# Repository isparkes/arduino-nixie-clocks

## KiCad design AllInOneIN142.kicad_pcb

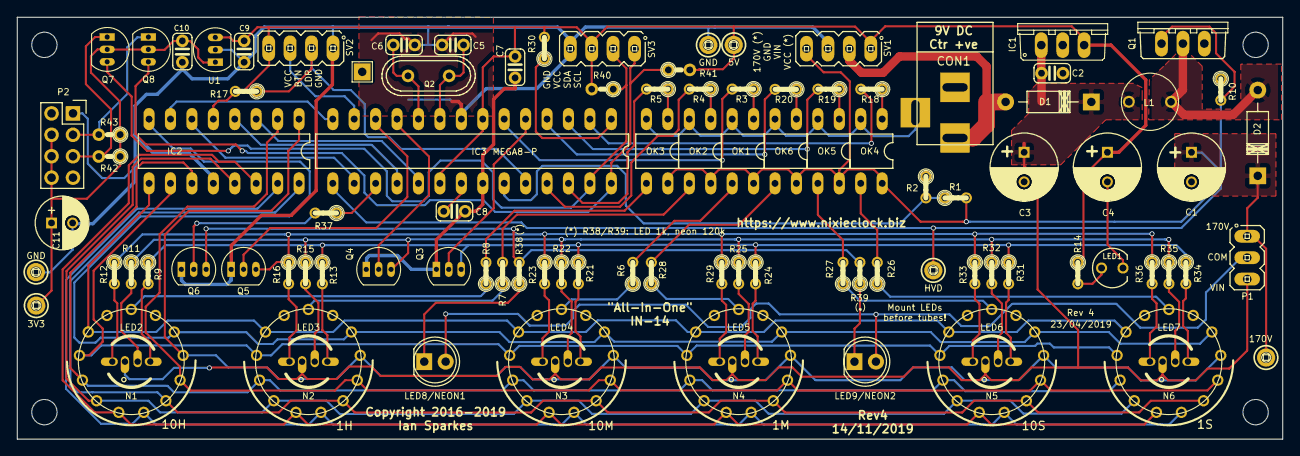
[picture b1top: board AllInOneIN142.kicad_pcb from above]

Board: 2 copper layers, 150.0 x 50.0 mm, 107 parts (0 on the bottom side), 88 nets.

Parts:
C1: 2.2uF; C_Radial_D8_L11.5_P3.5
C2, C7, C8, C9, C10: 100nF; C025-024X044
C3, C4: 220uF; C_Radial_D8_L11.5_P3.5
C5, C6: 22pF; C025-024X044
C11: 10uF; C_Radial_D6.3_L11.2_P2.5
CON1: BARREL_JACK
D1: 1N4001; Diode_DO-41_1N4001
D2: UF4004/7; Diode_DO-41_1N4001
GND Can: TestPoint_THTPad_2.0x2.0mm_Drill1.0mm
IC1: 7805; 7805_TO220V
IC2: 74141N; 74141_DIL16
IC3: MEGA8-P; 328P_DIL28
L1: 100uH; Inductor-100mH
LED1: Power; LED_3MM
LED2, LED3, LED4, LED5, LED6: LED_RAGB; LED5_RGB_CA_Offset_Tighter
LED7: LEDs2_RAGB; LED5_RGB_CA_Offset_Tighter
LED8/NEON1, LED9/NEON2: LED; LED-5MM-Centred
MH1, MH2, MH3, MH4: MountingHole_3mm
N1, N2, N3, N4, N5, N6: IN-14
OK1, OK2, OK3, OK4, OK5, OK6: EL817C; optocoupler-DIL04
P1: CONN_01X03; Header_MA03-1
P2: ESP8266-01_02X04; ESP8266_2x04
Q1: IRF840; TRANSISTOR-POWER_TO220BV
Q2: 16MHz; Crystal_HC49-U_Vertical
Q3, Q4, Q5, Q6: 2N7000; TO-92_inline_MPSA42
Q7, Q8: 2N7000; TO-92_2N7000_inline
R1: 390k; R-0207_2V
R2: 4.7k; R-0207_2V
R3, R4, R5, R9, R11, R12, R13, R15, R16, R18, R19, R20, R21, R22, R23, R24, R25, R29, R31, R32, R33, R34, R35, R36, R37, R38, R39: 1k; R-0207_2V
R6, R7, R8, R10, R14, R26, R27, R28: 3k; R-0207_2V
R17, R30, R40, R41, R42, R43: 10k; R-0207_2V
SV1: PWR; Header_MA04-1
SV2: CONN_FRONT; Header_MA04-1
SV3: CONN_RTC; Header_MA04-1
U1: L78L05_TO92; TO-92_2N7000_inline
W1: 5V; TESTPAD_P1-13
W2, W4: GND; TESTPAD_P1-13
W3: 170V; TESTPAD_P1-13
W5: HVD; TESTPAD_P1-13
W6: 3V3; TESTPAD_P1-13

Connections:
/3V3: C10.1, C11.1, P2.4, P2.6, P2.8, Q7.2, Q8.2, R42.1, R43.1, U1.1, W6.1
/170V: C1.1, D2.1, OK1.4, OK2.4, OK3.4, OK4.4, OK5.4, OK6.4, P1.1, R1.2, SV1.4, W3.1
/ANODE1: IC3.26, R5.2
/ANODE2: IC3.25, R4.2
/ANODE3: IC3.6, R3.2
/ANODE4: IC3.4, R20.2
/ANODE5: IC3.3, R19.2
/ANODE6: IC3.2, R18.2
/BTN1: IC3.13, SV2.3
/B_LED_DRIVE: Q3.3, R9.1, R13.1, R21.1, R24.1, R31.1, R34.1
/B_LED_GATE: IC3.5, Q3.2
/CATHODE_0: IC2.8, N1.0, N2.0, N3.0, N4.0, N5.0, N6.0
/CATHODE_1: IC2.9, N1.1, N2.1, N3.1, N4.1, N5.1, N6.1
/CATHODE_2: IC2.10, N1.2, N2.2, N3.2, N4.2, N5.2, N6.2
/CATHODE_3: IC2.11, N1.3, N2.3, N3.3, N4.3, N5.3, N6.3
/CATHODE_4: IC2.13, N1.4, N2.4, N3.4, N4.4, N5.4, N6.4
/CATHODE_5: IC2.14, N1.5, N2.5, N3.5, N4.5, N5.5, N6.5
/CATHODE_6: IC2.15, N1.6, N2.6, N3.6, N4.6, N5.6, N6.6
/CATHODE_7: IC2.16, N1.7, N2.7, N3.7, N4.7, N5.7, N6.7
/CATHODE_8: IC2.2, N1.8, N2.8, N3.8, N4.8, N5.8, N6.8
/CATHODE_9: IC2.1, N1.9, N2.9, N3.9, N4.9, N5.9, N6.9
/CON_AN_1: N1.A, R8.1
/CON_AN_2: N2.A, R7.1
/CON_AN_3: N3.A, R6.1
/CON_AN_4: N4.A, R28.1
/CON_AN_5: N5.A, R27.1
/CON_AN_6: N6.A, R26.1
/DIGIT_A: IC2.3, IC3.19
/DIGIT_B: IC2.6, IC3.16
/DIGIT_C: IC2.7, IC3.14
/DIGIT_D: IC2.4, IC3.18
/DLS: IC3.24, R17.1, SV2.2
/G_LED_DRIVE: Q4.3, R11.1, R15.1, R22.1, R25.1, R32.1, R35.1
/G_LED_GATE: IC3.11, Q4.2
/HVD: IC3.15, Q1.G, R10.2, W5.1
/HVS: IC3.23, R1.1, R2.2
/I_A1: OK3.1, R5.1
/I_A2: OK2.1, R4.1
/I_A3: OK1.1, R3.1
/I_A4: OK6.1, R20.1
/I_A5: OK5.1, R19.1
/I_A6: OK4.1, R18.1
/MOSI: IC3.17, R37.1
/O_A1: OK3.3, R8.2
/O_A2: OK2.3, R7.2
/O_A3: OK1.3, R6.2
/O_A4: OK6.3, R28.2
/O_A5: OK5.3, R27.2
/O_A6: OK4.3, R26.2
/PWR_HV_PULSE: D2.2, L1.1, Q1.D
/PWR_INPUT: CON1.1, D1.2, SV1.2
/PWR_VIN: C2.2, C3.1, D1.1, IC1.1, L1.2, LED2.2, LED3.2, LED4.2, LED5.2, LED6.2, LED7.2, P1.3
/RESET: IC3.1, R30.1
/R_LED_DRIVE: Q5.3, R12.1, R16.1, R23.1, R29.1, R33.1, R36.1
/R_LED_GATE: IC3.12, Q5.2
/SCL: IC3.28, Q8.3, R41.1, SV3.1
/SDA: IC3.27, Q7.3, R40.1, SV3.2
/TICK_LED_1: LED8/NEON1.1, R38.1
/TICK_LED_2: LED9/NEON2.1, R39.1
/TICK_LED_GATE: Q6.2, R37.2
/VCC: C4.1, C7.1, C9.1, IC1.3, IC2.5, IC3.7, IC3.20, R14.1, R17.2, R30.2, R40.2, R41.2, SV1.1, SV2.4, SV3.3, U1.3, W1.1
/XTAL1: C5.2, IC3.9, Q2.2
/XTAL2: C6.1, IC3.10, Q2.1
GND: C1.2, C2.1, C3.2, C4.2, C5.1, C6.2, C7.2, C8.1, C9.2, C10.2, C11.2, CON1.2, CON1.3, IC1.2, IC2.12, IC3.8, IC3.22, LED1.K, OK1.2, OK2.2, OK3.2, OK4.2, OK5.2, OK6.2, P2.1, Q1.S, Q3.1, Q4.1, Q5.1, Q6.1, R2.1, R10.1, SV1.3, SV2.1, SV3.4, U1.2, W2.1, W4.1
unnamed: C8.2, IC3.21
unnamed: LED1.A, R14.2
unnamed: LED2.1, R12.2
unnamed: LED2.3, R11.2
unnamed: LED2.4, R9.2
unnamed: LED3.1, R16.2
unnamed: LED3.3, R15.2
unnamed: LED3.4, R13.2
unnamed: LED4.1, R23.2
unnamed: LED4.3, R22.2
unnamed: LED4.4, R21.2
unnamed: LED5.1, R29.2
unnamed: LED5.3, R25.2
unnamed: LED5.4, R24.2
unnamed: LED6.1, R33.2
unnamed: LED6.3, R32.2
unnamed: LED6.4, R31.2
unnamed: LED7.1, R36.2
unnamed: LED7.3, R35.2
unnamed: LED7.4, R34.2
unnamed: LED8/NEON1.2, LED9/NEON2.2, P1.2
unnamed: P2.3, Q8.1, R43.2
unnamed: P2.5, Q7.1, R42.2
unnamed: Q6.3, R38.2, R39.2

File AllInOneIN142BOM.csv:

"Id";"Designator";"Package";"Quantity";"Designation";"Supplier and ref";
1;"W2,W2";"Measurement_Point_Round-TH_Big";2;"GND";;;
2;"C5,C6";"rcl-C050-024X044";2;"22pF";;;
3;"LED9,LED8";"LED-5MM-Centred";2;"LED";;;
4;"C1";"C_Radial_D8_L11.5_P3.5";1;"2.2uF";;;
5;"C3,C4";"C_Radial_D8_L11.5_P3.5";2;"220uF";;;
6;"W1";"Measurement_Point_Round-TH_Big";1;"VCC";;;
7;"W3";"Measurement_Point_Round-TH_Big";1;"170V";;;
8;"LED2,LED7,LED6,LED5,LED4,LED3";"LED5_RGB_CA";6;"LED_RAGB";;;
9;"Q2";"Crystal_HC49-U_Vertical";1;"16MHz";;;
10;"D2";"Diode_DO-41_1N4001";1;"UF4004/7";;;
11;"D1";"Diode_DO-41_1N4001";1;"1N4001";;;
12;"REF**,REF**,REF**,REF**";"MountingHole_3mm";4;"MountingHole_3mm";;;
13;"IC2";"74141_DIL16";1;"74141N";;;
14;"R2";"R-0207_2V";1;"4.7k";;;
15;"R1";"R-0207_2V";1;"390k";;;
16;"R14,R7,R8,R28,R27,R26,R6,R10";"R-0207_2V";8;"3k";;;
17;"R13,R12,R9,R11,R3,R19,R18,R23,R39,R20,R21,R22,R24,R25,R29,R31,R32,R33,R34,R35,R36,R37,R38,R4,R5,R15,R16";"R-0207_2V";27;"1k";;;
18;"R30,R17";"R-0207_2V";2;"10k";;;
19;"IC3";"328P_DIL28";1;"MEGA8-P";;;
20;"OK1,OK2,OK3,OK4,OK5,OK6";"optocoupler-DIL04";6;"EL817C";;;
21;"SV2";"Header_MA04-1";1;"CONN_FRONT";;;
22;"SV3";"Header_MA04-1";1;"CONN_RTC";;;
23;"SV1";"Header_MA04-1";1;"PWR";;;
24;"Q3,Q4,Q5,Q6";"2N7000_TO92";4;"2N7000";;;
25;"C7,C2,C8";"rcl-C050-024X044";3;"100nF";;;
26;"P1";"Header_MA03-1";1;"CONN_01X03";;;
27;"LED1";"LED_3MM";1;"Power";;;
28;"L1";"Inductor-100mH";1;"100uH";;;
29;"IC1";"7805_TO220V";1;"7805";;;
30;"Q1";"TRANSISTOR-POWER_TO220BV";1;"IRF740";;;
31;"N2,N5,N4,N3,N6,N1";"IN-14";6;"IN-14";;;

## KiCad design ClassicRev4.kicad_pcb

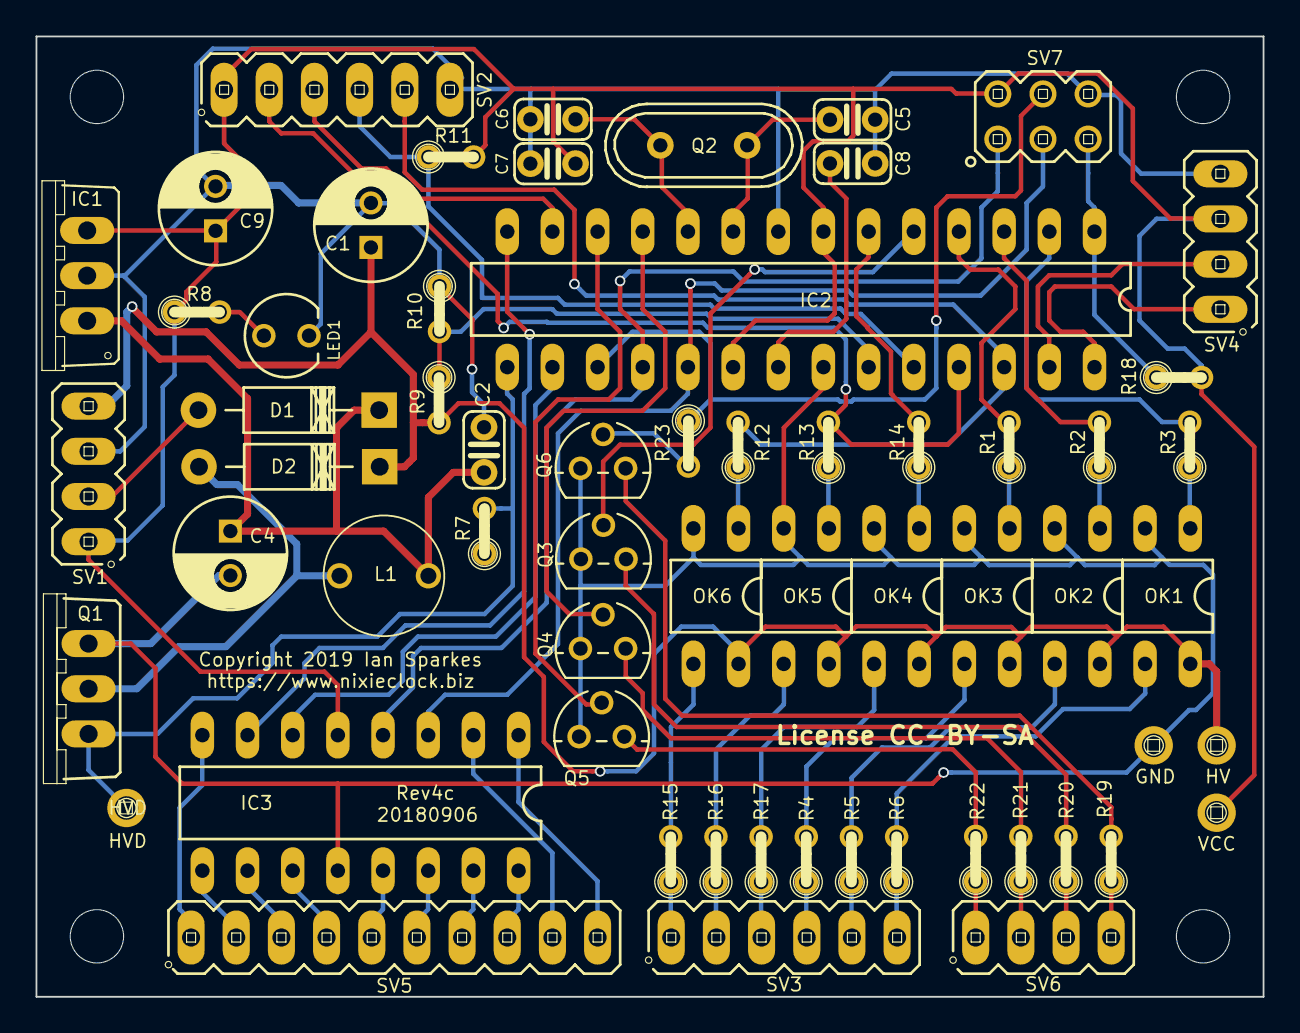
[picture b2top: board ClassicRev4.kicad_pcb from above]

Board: 2 copper layers, 69.0 x 54.0 mm, 65 parts (0 on the bottom side), 68 nets.

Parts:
C1: 2.2uF; C_Radial_D6.3_L11.2_P2.5
C2, C7, C8: 100nF; C025-024X044
C4, C9: 220uF; C_Radial_D6.3_L11.2_P2.5
C5, C6: 22pF; C025-024X044
D1: 1N4001; Diode_DO-41_1N4001
D2: UF4007; Diode_DO-41_1N4001
IC1: 7805TV; 7805_TO220V
IC2: MEGA8-P; 328P_DIL28
IC3: K155ID1; 74141_DIL16
L1: 100uH; Inductor-100mH
LED1: Power; LED_3MM
MH1, MH2, MH3, MH4: MountingHole_3mm
OK1, OK2, OK3, OK4, OK5, OK6: EL817C; optocoupler-DIL04
Q1: IRF740; TRANSISTOR-POWER_TO220BV
Q2: 16MHz; Crystal_HC49-U_Vertical
Q3, Q4, Q5, Q6: 2N7000; 2N7000_TO92
R1, R2, R3, R12, R13, R14, R19, R20, R21, R22, R23: 1k; R-0207_2V
R4, R5, R6, R7, R8, R15, R16, R17: 2.7k; R-0207_2V
R9: 390k; R-0207_2V
R10: 4.7k; R-0207_2V
R11, R18: 10k; R-0207_2V
SV1: PWR; Header_MA04-1
SV2: CONN_FRONT; Header_MA06-1
SV3: CONN_01X06; Header_MA06-1
SV4: CONN_RTC; Header_MA04-1
SV5: CONN_01X10; Header_MA10-1
SV6: CONN_LED; Header_MA04-1
SV7: CONN_ISCP; Header_MA03-2
TP1: HV; TESTPAD_P1-13
TP2: GND; TESTPAD_P1-13
TP3: VCC; TESTPAD_P1-13
TP4: HVD; TESTPAD_P1-13

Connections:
/170V: C1.1, D2.1, OK1.4, OK2.4, OK3.4, OK4.4, OK5.4, OK6.4, R9.2, SV1.4, TP1.1
/ANODE1: IC2.2, R3.2
/ANODE2: IC2.3, R2.2
/ANODE3: IC2.4, R1.2
/ANODE4: IC2.6, R14.2
/ANODE5: IC2.25, R13.2, SV2.2
/ANODE6: IC2.26, R12.2, SV2.5
/AREF: C8.2, IC2.21
/BTN1: IC2.13, SV2.3
/B_GATE: IC2.5, Q3.2
/B_LED: R20.1, SV6.3
/CATHODE_0: IC3.8, SV5.1
/CATHODE_1: IC3.9, SV5.2
/CATHODE_2: IC3.10, SV5.3
/CATHODE_3: IC3.11, SV5.4
/CATHODE_4: IC3.13, SV5.5
/CATHODE_5: IC3.14, SV5.6
/CATHODE_6: IC3.15, SV5.7
/CATHODE_7: IC3.16, SV5.8
/CATHODE_8: IC3.2, SV5.9
/CATHODE_9: IC3.1, SV5.10
/DIGIT_A: IC2.19, IC3.3, SV7.3
/DIGIT_B: IC2.16, IC3.6
/DIGIT_C: IC2.14, IC3.7
/DIGIT_D: IC2.18, IC3.4, SV7.1
/DLS: IC2.24, R11.1, SV2.4
/DRAIN: D2.2, L1.1, Q1.D
/G_GATE: IC2.11, Q4.2
/G_LED: R21.1, SV6.2
/HVD: IC2.15, Q1.G, R7.2, TP4.1
/HVS: IC2.23, R9.1, R10.2
/MOSI: IC2.17, R23.1, SV7.4
/RESET: IC2.1, R18.1, SV7.5
/R_GATE: IC2.12, Q5.2
/R_LED: R22.1, SV6.1
/SCL: IC2.28, SV4.1
/SDA: IC2.27, SV4.2
/TICK_BASE: Q6.2, R23.2
/TICK_LED: R19.1, SV6.4
/VCC: C7.1, C9.1, IC1.3, IC2.7, IC2.20, IC3.5, R8.1, R11.2, R18.2, SV1.1, SV2.1, SV4.3, SV7.2, TP3.1
/VIN: C2.2, C4.1, D1.1, IC1.1, L1.2
/XTAL1: C5.2, IC2.9, Q2.2
/XTAL2: C6.1, IC2.10, Q2.1
GND: C1.2, C2.1, C4.2, C5.1, C6.2, C7.2, C8.1, C9.2, IC1.2, IC2.8, IC2.22, IC3.12, LED1.K, OK1.2, OK2.2, OK3.2, OK4.2, OK5.2, OK6.2, Q1.S, Q3.3, Q4.3, Q5.3, Q6.3, R7.1, R10.1, SV1.3, SV2.6, SV4.4, SV7.6, TP2.1
unnamed: D1.2, SV1.2
unnamed: LED1.A, R8.2
unnamed: OK1.1, R3.1
unnamed: OK1.3, R6.2
unnamed: OK2.1, R2.1
unnamed: OK2.3, R5.2
unnamed: OK3.1, R1.1
unnamed: OK3.3, R4.2
unnamed: OK4.1, R14.1
unnamed: OK4.3, R17.2
unnamed: OK5.1, R13.1
unnamed: OK5.3, R16.2
unnamed: OK6.1, R12.1
unnamed: OK6.3, R15.2
unnamed: Q3.1, R20.2
unnamed: Q4.1, R21.2
unnamed: Q5.1, R22.2
unnamed: Q6.1, R19.2
unnamed: R4.1, SV3.4
unnamed: R5.1, SV3.5
unnamed: R6.1, SV3.6
unnamed: R15.1, SV3.1
unnamed: R16.1, SV3.2
unnamed: R17.1, SV3.3

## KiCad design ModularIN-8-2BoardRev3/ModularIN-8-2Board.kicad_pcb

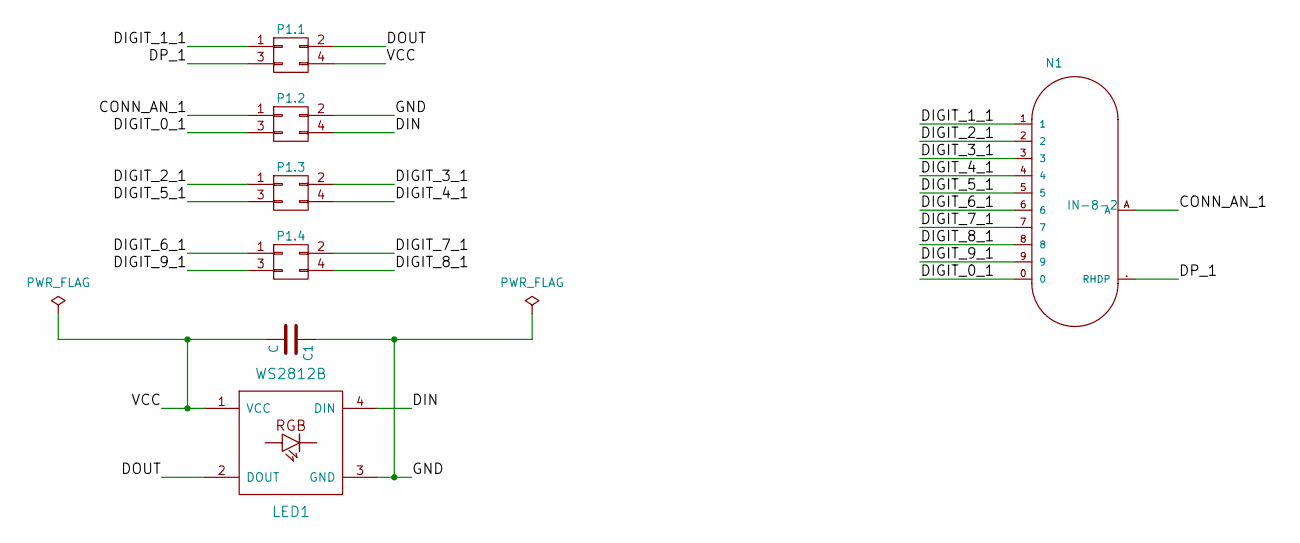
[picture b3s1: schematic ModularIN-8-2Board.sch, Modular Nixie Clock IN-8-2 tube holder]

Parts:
C1: C; C_1206_HandSoldering
LED1: WS2812B
N1: IN-8-2
P1.1, P1.2, P1.3, P1.4: CONN_02X02; Header_MA02-2

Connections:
/CONN_AN_1: N1.A, P1.2.1
/DIGIT_0_1: N1.0, P1.2.3
/DIGIT_1_1: N1.1, P1.1.1
/DIGIT_2_1: N1.2, P1.3.1
/DIGIT_3_1: N1.3, P1.3.2
/DIGIT_4_1: N1.4, P1.3.4
/DIGIT_5_1: N1.5, P1.3.3
/DIGIT_6_1: N1.6, P1.4.1
/DIGIT_7_1: N1.7, P1.4.2
/DIGIT_8_1: N1.8, P1.4.4
/DIGIT_9_1: N1.9, P1.4.3
/DIN: LED1.4 (DIN), P1.2.4
/DOUT: LED1.2 (DOUT), P1.1.2
/DP_1: N1.. (RHDP), P1.1.3
/GND: C1.1, LED1.3 (GND), P1.2.2
/VCC: C1.2, LED1.1 (VCC), P1.1.4

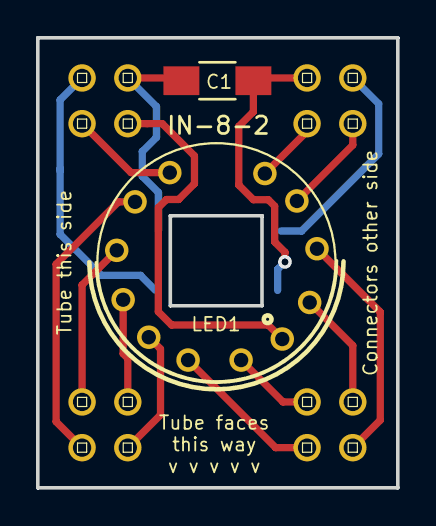
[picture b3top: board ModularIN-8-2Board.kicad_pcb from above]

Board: 2 copper layers, 20.0 x 25.0 mm, 7 parts (0 on the bottom side), 16 nets.

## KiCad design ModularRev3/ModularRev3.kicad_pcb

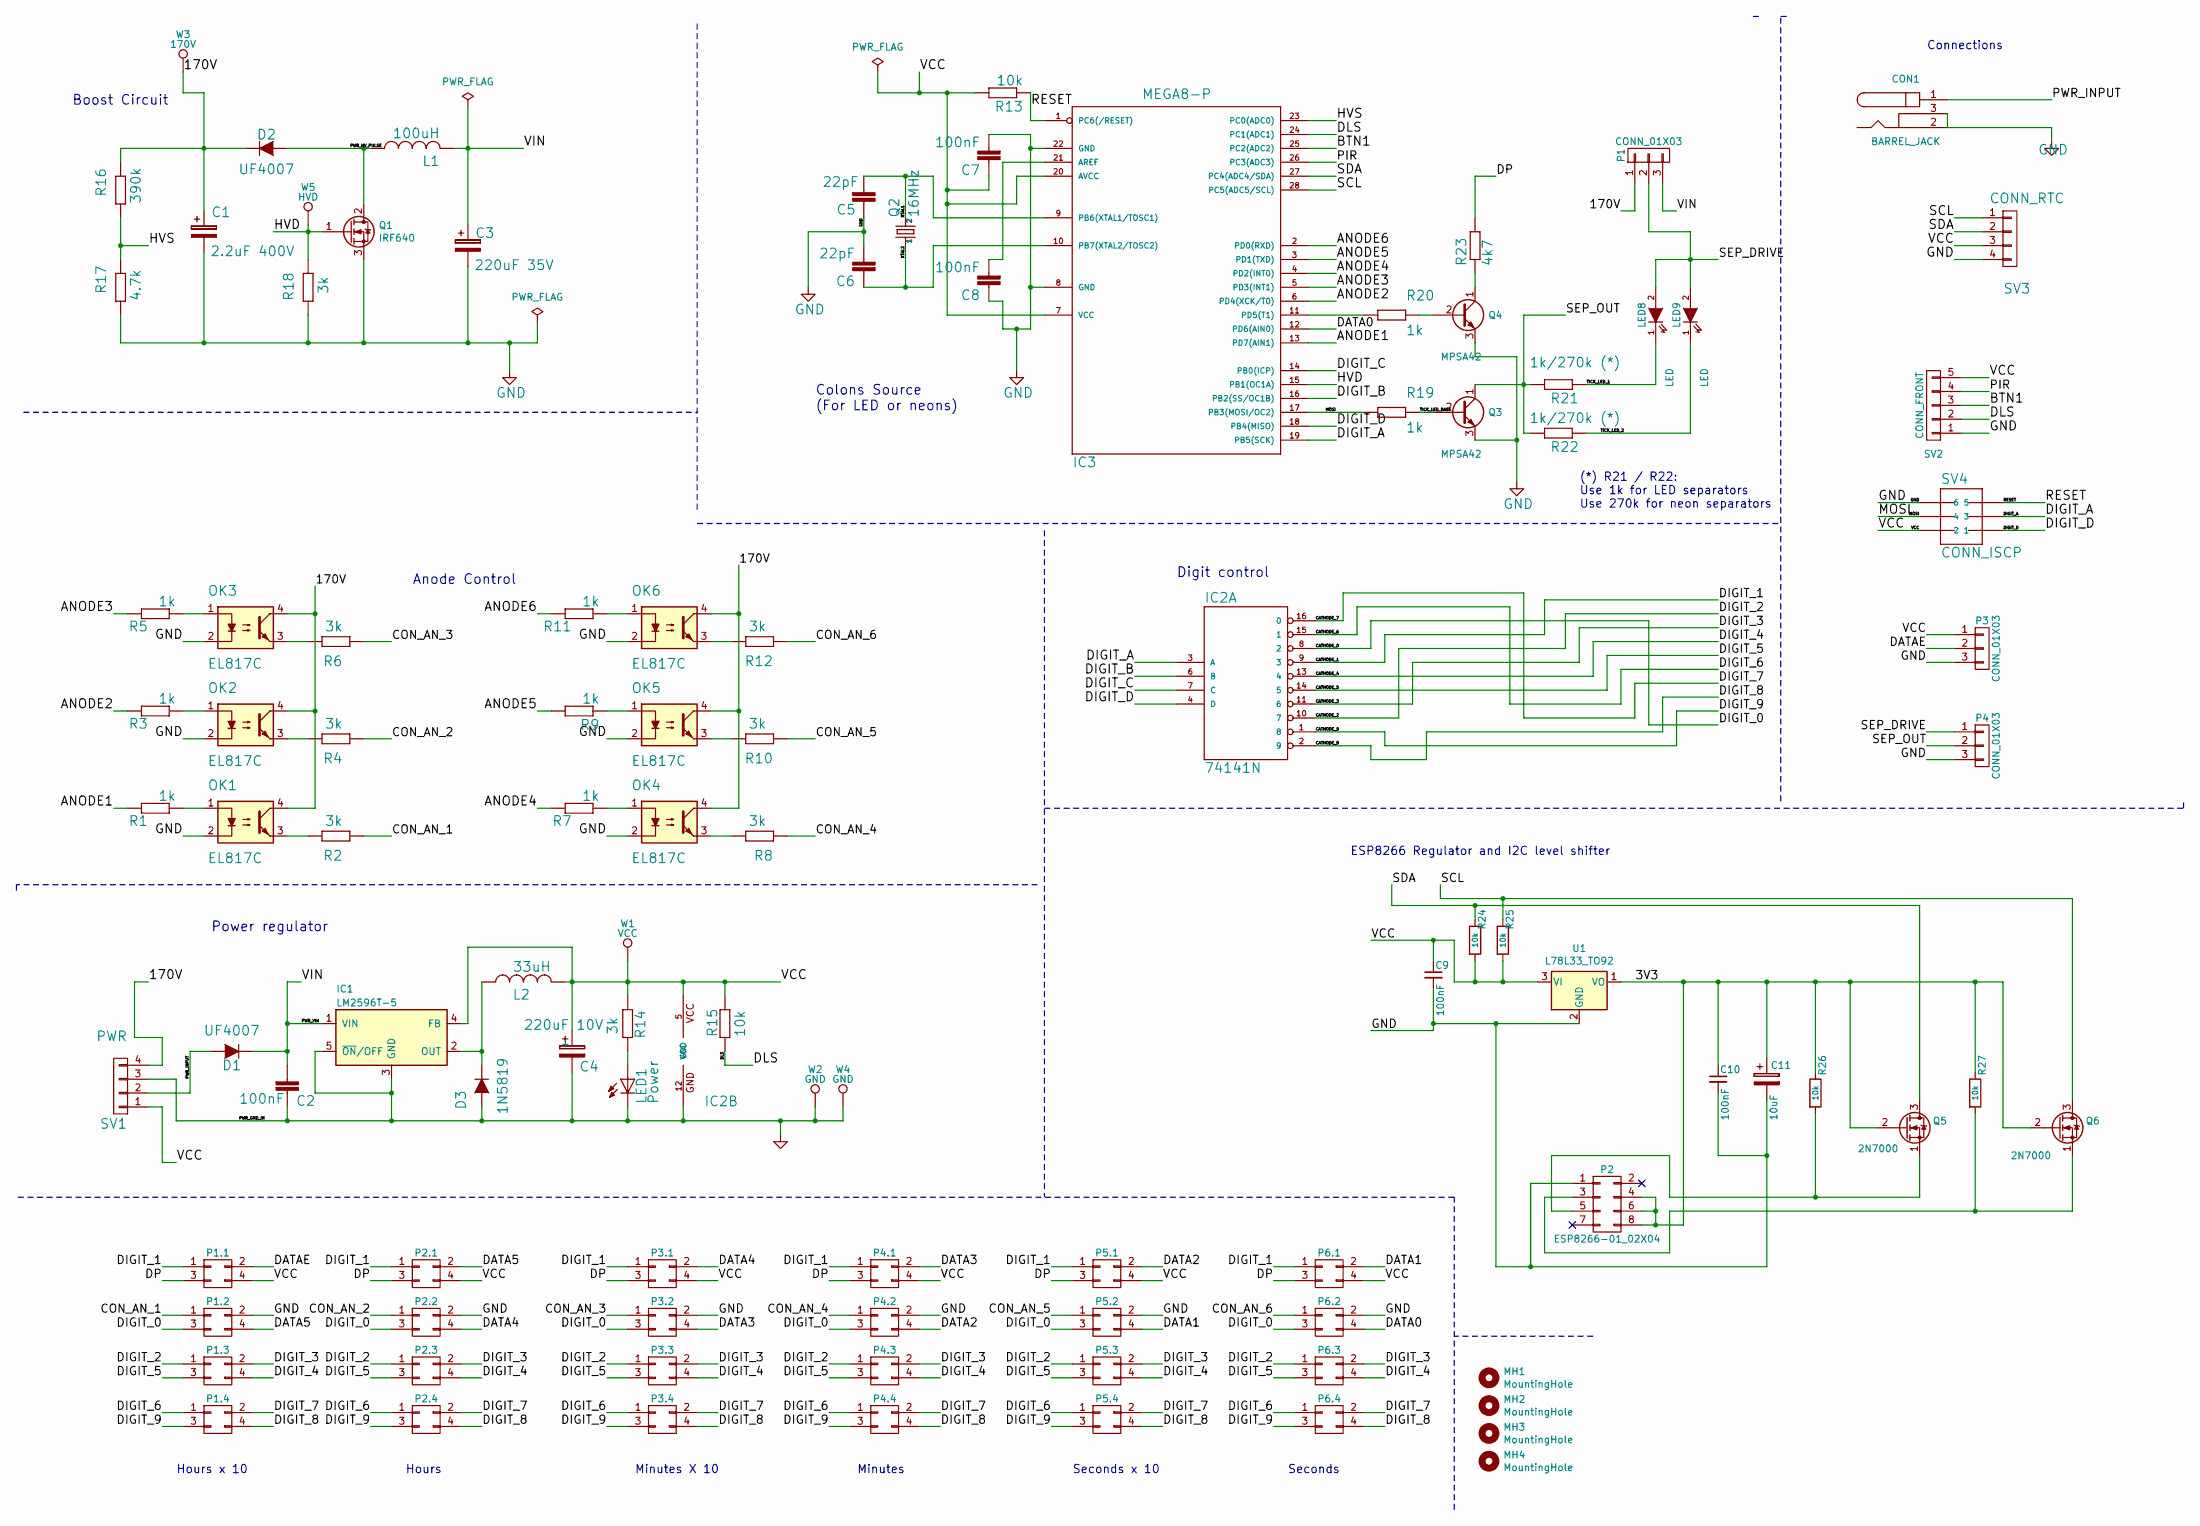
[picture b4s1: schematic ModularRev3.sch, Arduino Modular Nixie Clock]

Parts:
C1: 2.2uF 400V; C_Radial_D10_L11.2_P2.5_3.5_5
C2, C7, C8, C9, C10: 100nF; C025-024X044
C3: 220uF 35V; C_Radial_D6.3_L11.2_P2.5
C4: 220uF 10V; C_Radial_D6.3_L11.2_P2.5
C5, C6: 22pF; C025-024X044
C11: 10uF; C_Radial_D6.3_L11.2_P2.5
CON1: BARREL_JACK
D1, D2: UF4007; Diode_DO-41_1N4001
D3: 1N5819; Diode_DO-41_1N4001
IC1: LM2596T-5; TO220-5A
IC2: 74141N; 74141_DIL16
IC3: MEGA8-P; 328P_DIL28
L1: 100uH; Inductor-100mH
L2: 33uH; Inductor-33mH-TH-SMD
LED1: Power; LED_3MM
LED8, LED9: LED; LED-5MM-Centred
MH1, MH2, MH3, MH4: MountingHole; MountingHole_3.2mm_M3
OK1, OK2, OK3, OK4, OK5, OK6: EL817C; optocoupler-DIL04
P1, P3, P4: CONN_01X03; Header_MA03-1
P1.1, P1.2, P1.3, P1.4, P2.1, P2.2, P2.3, P2.4, P3.1, P3.2, P3.3, P3.4, P4.1, P4.2, P4.3, P4.4, P5.1, P5.2, P5.3, P5.4, P6.1, P6.2, P6.3, P6.4: CONN_02X02; Header_MA02-2
P2: ESP8266-01_02X04; ESP8266_2x04
Q1: IRF640; TO-220-3_H
Q2: 16MHz; Crystal_HC49-U_Vertical
Q3, Q4: MPSA42; 2N7000_TO92
Q5, Q6: 2N7000; TO-92_2N7000_inline
R1, R3, R5, R7, R9, R11, R19, R20: 1k; R-0207_2V
R2, R4, R6, R8, R10, R12, R14, R18: 3k; R-0207_2V
R13, R15, R24, R25, R26, R27: 10k; R-0207_2V
R16: 390k; R-0207_2V
R17: 4.7k; R-0207_2V
R21, R22: 1k/270k (*); R-0207_2V
R23: 4k7; R-0207_2V
SV1: PWR; Header_MA04-1
SV2: CONN_FRONT; Header_MA05-1
SV3: CONN_RTC; Header_MA04-1
SV4: CONN_ISCP; Header_MA03-2
U1: L78L33_TO92; TO-92_Inline
W1: VCC; TESTPAD_P1-13
W2, W4: GND; TESTPAD_P1-13
W3: 170V; TESTPAD_P1-13
W5: HVD; TESTPAD_P1-13

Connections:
/3V3: C10.1, C11.1, P2.4 (CH_EN), P2.6 (RST), P2.8 (VCC), Q5.2 (G), Q6.2 (G), R26.1, R27.1, U1.1 (VO)
/170V: C1.1, D2.1 (K), OK1.4, OK2.4, OK3.4, OK4.4, OK5.4, OK6.4, P1.1, R16.2, SV1.4, W3.1
/ANODE1: IC3.13 (PD7(AIN1)), R1.2
/ANODE2: IC3.6 (PD4(XCK/T0)), R3.2
/ANODE3: IC3.5 (PD3(INT1)), R5.2
/ANODE4: IC3.4 (PD2(INT0)), R7.2
/ANODE5: IC3.3 (PD1(TXD)), R9.2
/ANODE6: IC3.2 (PD0(RXD)), R11.2
/BTN1: IC3.25 (PC2(ADC2)), SV2.3
/CATHODE_0: IC2.8 (2), P1.2.3, P2.2.3, P3.2.3, P4.2.3, P5.2.3, P6.2.3
/CATHODE_1: IC2.9 (3), P1.1.1, P2.1.1, P3.1.1, P4.1.1, P5.1.1, P6.1.1
/CATHODE_2: IC2.10 (7), P1.3.1, P2.3.1, P3.3.1, P4.3.1, P5.3.1, P6.3.1
/CATHODE_3: IC2.11 (6), P1.3.2, P2.3.2, P3.3.2, P4.3.2, P5.3.2, P6.3.2
/CATHODE_4: IC2.13 (4), P1.3.4, P2.3.4, P3.3.4, P4.3.4, P5.3.4, P6.3.4
/CATHODE_5: IC2.14 (5), P1.3.3, P2.3.3, P3.3.3, P4.3.3, P5.3.3, P6.3.3
/CATHODE_6: IC2.15 (1), P1.4.1, P2.4.1, P3.4.1, P4.4.1, P5.4.1, P6.4.1
/CATHODE_7: IC2.16 (0), P1.4.2, P2.4.2, P3.4.2, P4.4.2, P5.4.2, P6.4.2
/CATHODE_8: IC2.2 (9), P1.4.4, P2.4.4, P3.4.4, P4.4.4, P5.4.4, P6.4.4
/CATHODE_9: IC2.1 (8), P1.4.3, P2.4.3, P3.4.3, P4.4.3, P5.4.3, P6.4.3
/CON_AN_1: P1.2.1, R2.1
/CON_AN_2: P2.2.1, R4.1
/CON_AN_3: P3.2.1, R6.1
/CON_AN_4: P4.2.1, R8.1
/CON_AN_5: P5.2.1, R10.1
/CON_AN_6: P6.2.1, R12.1
/DATA0: IC3.12 (PD6(AIN0)), P6.2.4
/DATA1: P5.2.4, P6.1.2
/DATA2: P4.2.4, P5.1.2
/DATA3: P3.2.4, P4.1.2
/DATA4: P2.2.4, P3.1.2
/DATA5: P1.2.4, P2.1.2
/DATAE: P1.1.2, P3.2
/DIGIT_A: IC2.3 (A), IC3.19 (PB5(SCK)), SV4.3
/DIGIT_B: IC2.6 (B), IC3.16 (PB2(SS/OC1B))
/DIGIT_C: IC2.7 (C), IC3.14 (PB0(ICP))
/DIGIT_D: IC2.4 (D), IC3.18 (PB4(MISO)), SV4.1
/DLS: IC3.24 (PC1(ADC1)), R15.1, SV2.2
/DP: P1.1.3, P2.1.3, P3.1.3, P4.1.3, P5.1.3, P6.1.3, R23.2
/HVD: IC3.15 (PB1(OC1A)), Q1.1 (G), R18.2, W5.1
/HVS: IC3.23 (PC0(ADC0)), R16.1, R17.2
/MOSI: IC3.17 (PB3(MOSI/OC2)), R19.1, SV4.4
/PIR: IC3.26 (PC3(ADC3)), SV2.4
/PWR_HV_PULSE: D2.2 (A), L1.1, Q1.2 (D)
/PWR_INPUT: CON1.1, D1.2 (A), SV1.2
/PWR_VIN: C2.2, C3.1, D1.1 (K), IC1.1 (VIN), L1.2, P1.3
/RESET: IC3.1 (PC6(/RESET)), R13.1, SV4.5
/SCL: IC3.28 (PC5(ADC5/SCL)), Q6.3 (D), R25.1, SV3.1
/SDA: IC3.27 (PC4(ADC4/SDA)), Q5.3 (D), R24.1, SV3.2
/SEP_DRIVE: LED8.2 (A), LED9.2 (A), P1.2, P4.1
/SEP_OUT: P4.2, Q3.1 (C), R21.2, R22.2
/TICK_LED_1: LED8.1 (K), R21.1
/TICK_LED_2: LED9.1 (K), R22.1
/TICK_LED_BASE: Q3.2 (B), R19.2
/VCC: C4.1, C7.1, C9.1, IC1.4 (FB), IC2.5 (VCC), IC3.7 (VCC), IC3.20 (AVCC), L2.2, P1.1.4, P2.1.4, P3.1, P3.1.4, P4.1.4, P5.1.4, P6.1.4, R13.2, R14.1, R15.2, R24.2, R25.2, SV1.1, SV2.5, SV3.3, SV4.2, U1.3 (VI), W1.1
/XTAL1: C5.2, IC3.9 (PB6(XTAL1/TOSC1)), Q2.2
/XTAL2: C6.1, IC3.10 (PB7(XTAL2/TOSC2)), Q2.1
GND: C1.2, C2.1, C3.2, C4.2, C5.1, C6.2, C7.2, C8.1, C9.2, C10.2, C11.2, CON1.2, CON1.3, D3.2 (A), IC1.3 (GND), IC1.5 (~ON~/OFF), IC2.12 (GND), IC3.8 (GND), IC3.22 (GND), LED1.K (C), OK1.2, OK2.2, OK3.2, OK4.2, OK5.2, OK6.2, P1.2.2, P2.1 (GND), P2.2.2, P3.3, P3.2.2, P4.3, P4.2.2, P5.2.2, P6.2.2, Q1.3 (S), Q3.3 (E), Q4.3 (E), R17.1, R18.1, SV1.3, SV2.1, SV3.4, SV4.6, U1.2 (GND), W2.1, W4.1
unnamed: C8.2, IC3.21 (AREF)
unnamed: D3.1 (K), IC1.2 (OUT), L2.1
unnamed: IC3.11 (PD5(T1)), R20.1
unnamed: LED1.A, R14.2
unnamed: OK1.1, R1.1
unnamed: OK1.3, R2.2
unnamed: OK2.1, R3.1
unnamed: OK2.3, R4.2
unnamed: OK3.1, R5.1
unnamed: OK3.3, R6.2
unnamed: OK4.1, R7.1
unnamed: OK4.3, R8.2
unnamed: OK5.1, R9.1
unnamed: OK5.3, R10.2
unnamed: OK6.1, R11.1
unnamed: OK6.3, R12.2
unnamed: P2.3 (GPIO2), Q6.1 (S), R27.2
unnamed: P2.5 (GPIO0), Q5.1 (S), R26.2
unnamed: Q4.1 (C), R23.1
unnamed: Q4.2 (B), R20.2

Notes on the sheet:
Boost Circuit
Anode Control
Power regulator
Digit control
Colons Source (For LED or neons)
Seconds
Seconds x 10
Minutes
Minutes X 10
Hours
Hours x 10
ESP8266 Regulator and I2C level shifter
Connections
(*) R21 / R22: Use 1k for LED separators Use 270k for neon separators

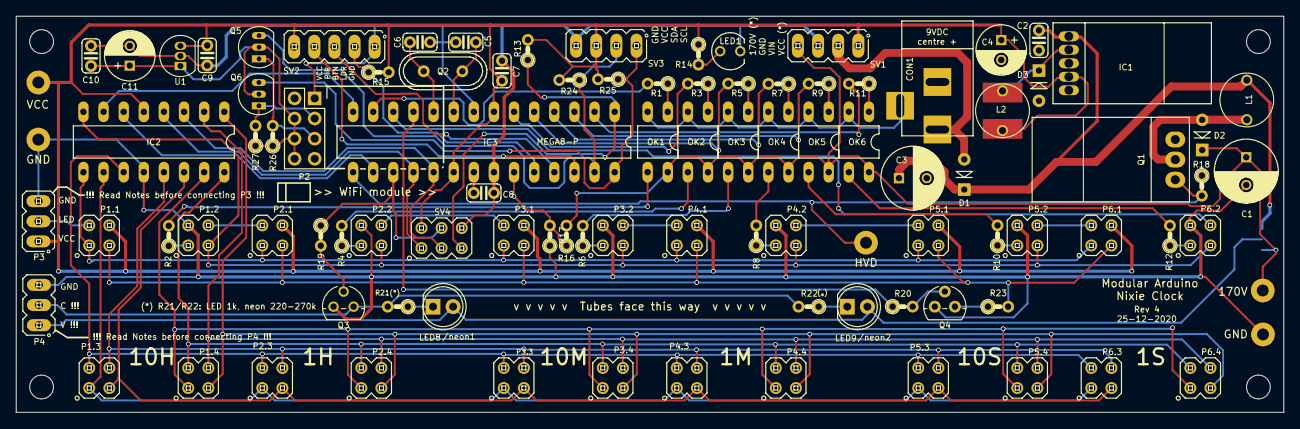
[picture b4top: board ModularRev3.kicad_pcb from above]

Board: 2 copper layers, 160.0 x 50.0 mm, 104 parts (1 on the bottom side), 77 nets.

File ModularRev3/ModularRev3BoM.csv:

"Id";"Designator";"Package";"Quantity";"Designation";"Supplier and ref";
1;"IC3";"328P_DIL28";1;"MEGA8-P";;;
2;"D3";"Diode_DO-41_SOD81_Vertical_KathodeUp";1;"1N5819";;;
3;"R21,R5,R9,R11,R22,R7,R3,R1,R19,R20";"R-0207_2V";10;"1k";;;
4;"R4,R14,R2,R8,R10,R12,R6,R18";"R-0207_2V";8;"3k";;;
5;"C4,C3";"C_Radial_D8_L11.5_P3.5";2;"220uF";;;
6;"W2";"Measurement_Point_Round-TH_Big";1;"GND";;;
7;"W1";"Measurement_Point_Round-TH_Big";1;"VCC";;;
8;"Q2";"Crystal_HC49-U_Vertical";1;"16MHz";;;
9;"MH4,MH3,MH1,MH2";"MountingHole_3mm";4;"MountingHole_3mm";;;
10;"IC2";"74141_DIL16";1;"K155ID1";;;
11;"R17";"R-0207_2V";1;"4.7k";;;
12;"R16";"R-0207_2V";1;"390k";;;
13;"R13,R15";"R-0207_2V";2;"10k";;;
14;"OK3,OK2,OK1,OK6,OK5,OK4";"optocoupler-DIL04";6;"EL817C";;;
15;"SV3";"Header_MA04-1";1;"CONN_RTC";;;
16;"SV1";"Header_MA04-1";1;"PWR";;;
17;"Q3,Q4";"2N7000_TO92";2;"MPSA42";;;
18;"P1";"Header_MA03-1";1;"CONN_01X03";;;
19;"LED1";"LED_3MM";1;"Power";;;
20;"L1";"Inductor-100mH";1;"100uH";;;
21;"CON1";"BARREL_JACK";1;"BARREL_JACK";;;
22;"D1,D2";"Diode_DO-41_SOD81_Vertical_KathodeUp";2;"UF4007";;;
23;"IC1";"TO220-5A";1;"LM2596T-5";;;
24;"L2";"Inductor-33mH-TH-SMD";1;"33uH";;;
25;"C6,C5";"C025-024X044";2;"22pF";;;
26;"C8,C2,C7";"C025-024X044";3;"100nF";;;
27;"C1";"C_Radial_D10_L11.2_P2.5_3.5_5";1;"10uF";;;
28;"P1.1,P1.2,P1.3,P1.4,P2.1,P2.2,P2.3,P2.4,P3.1,P3.2,P3.3,P3.4,P4.1,P4.2,P4.3,P4.4,P5.1,P5.2,P5.3,P5.4,P6.1,P6.2,P6.3,P6.4";"Header_MA02-2";24;"CONN_02X02";;;
29;"LED8,LED9";"LED-5MM-Centred";2;"LED";;;
30;"R23";"R-0207_2V";1;"120k";;;
31;"P2";"Socket_Strip_Straight_2x04";1;"ESP8266-01_02X04";;;
32;"Q5,Q6";"SOT-23_Handsoldering";2;"BSS138";;;
33;"SV4";"Header_MA03-2";1;"CONN_ISCP";;;
34;"U1";"SOT-223";1;"AP1117";;;
35;"R24,R26,R27,R25";"R_1206_HandSoldering";4;"10k";;;
36;"C9,C10";"C_1206_HandSoldering";2;"100nF";;;
37;"C11";"C_1206_HandSoldering";1;"10uF";;;
38;"SV2";"Header_MA05-1";1;"CONN_FRONT";;;
39;"P3,P4";"Header_MA03-1";2;"CONN_01X03";;;
40;"W3";"Measurement_Point_Round-TH_Big";1;"170V";;;
41;"W5";"Measurement_Point_Round-TH_Big";1;"HVD";;;
42;"W4";"Measurement_Point_Round-TH_Big";1;"GND";;;
43;"Q1";"TRANSISTOR-POWER_TO220BV";1;"IRF840";;;

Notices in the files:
AllInOneIN142.kicad_pcb:
Copyright 2016-2019
ClassicRev4.kicad_pcb:
License CC-BY-SA
Copyright 2019 Ian Sparkes
ModularRev3/ModularRev3.kicad_pcb:
Copyright 2017-2020 Ian Sparkes
